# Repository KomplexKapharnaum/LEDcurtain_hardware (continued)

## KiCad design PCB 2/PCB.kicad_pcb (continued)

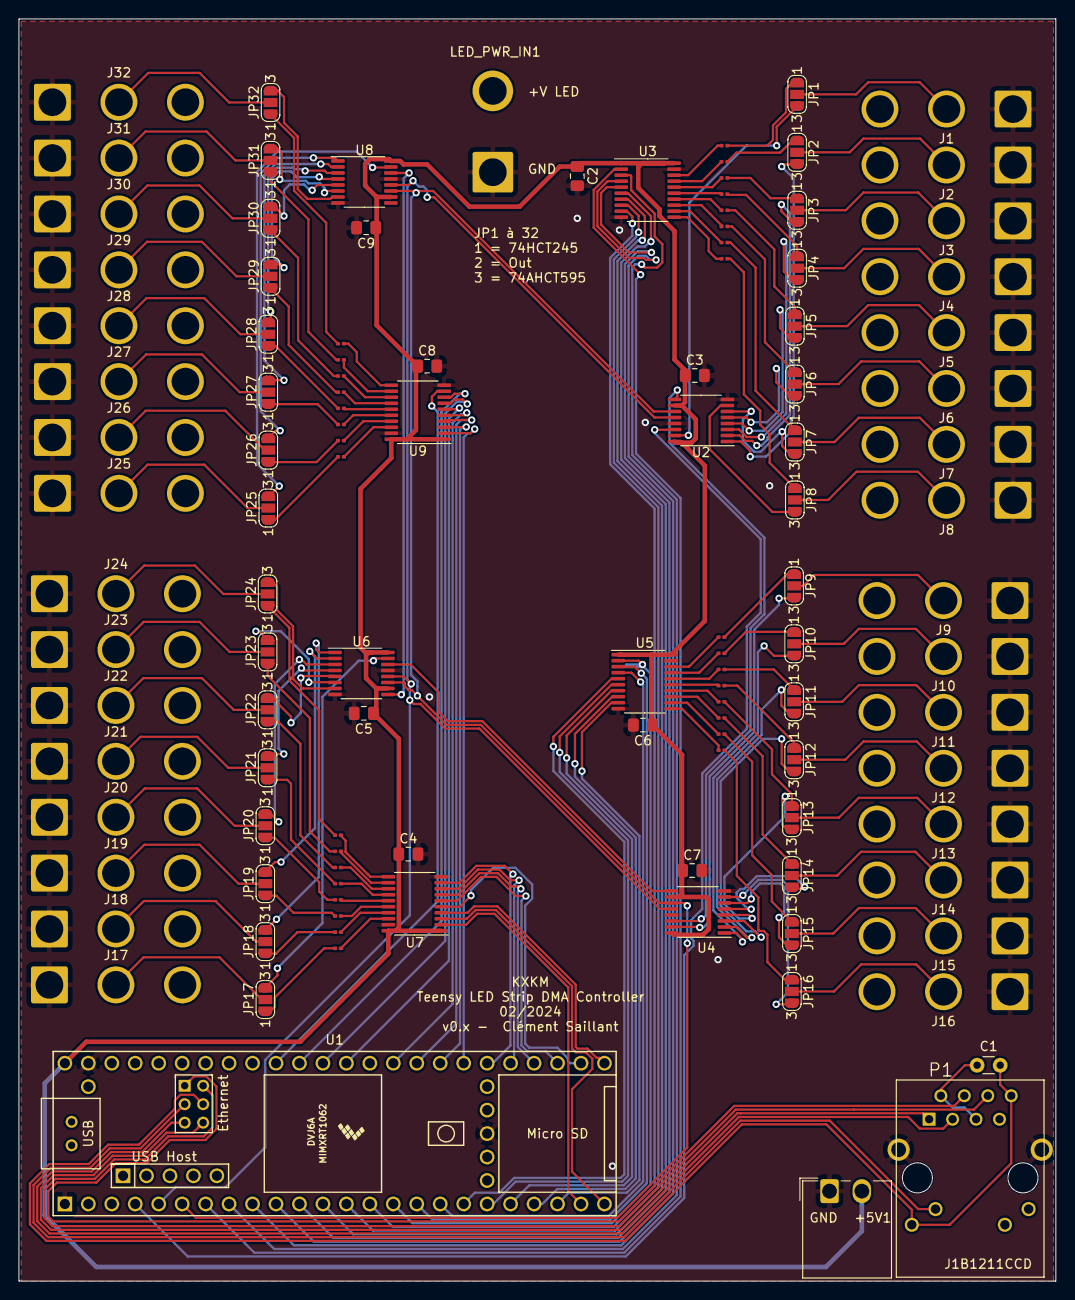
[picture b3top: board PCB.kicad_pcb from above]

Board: 2 copper layers, 112.3 x 136.7 mm, 117 parts (0 on the bottom side), 176 nets.

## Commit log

2025-01-21 update pcb v2 abd step file
2025-02-10 update PCB
